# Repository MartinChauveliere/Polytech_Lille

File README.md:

# Projets Polytech Lille

Ce dépôt contient les projets réalisés dans le cadre de mes études à Polytech Lille, mon école d'ingénierie en France. 
Vous y trouverez différents projets liés à des domaines comme l'électronique, le code, et la conception de PCB.

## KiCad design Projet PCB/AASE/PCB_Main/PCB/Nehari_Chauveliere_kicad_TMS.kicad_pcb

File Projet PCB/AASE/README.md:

# AASE_Nehari_Chauveliere

## Objectif

L'obejctif initial de ce projet est de concevoir et réaliser la partie récepton d'une chaîne de réception en modulation numérique BPSK.

## Kicad schématique

Tout d'abord, nous avons dû créer notre carte électronique sur Kicad, pour cela nous sommes partis du précédent projet réalisé en TMS. De ce projet nous avons conservé le microcontrôleur (STM32) et le capteur de température (MCP9000) principalement.

Nous avons ensuite ajouté ce dont on avait besoin, c'est-à-dire :
- Quartz haute fréquence pour le STM32, MCSJK-7U-32.00-10-30-60-B-30;
- LDO positif pour convertir du +15V venant d'un générateur en +8V pour le démodulateur, AP7333-33SAG-7;
- LDO négatif pour convertir du -15V venant d'un générateur en -8V pour le démodulateur, MIC5271YM5-TR;
- Mosfet de puissance, XP161A1355PR-G;
- Convertisseur boost pour convertir du +1.8V venant d'une batterie vers du +3.3V, XC9103D095MR-G;
- Diode schottky pour le convertisseur boost, D0-214AC;
- Connecteurs divers.

## Kicad Rootage

Nous avons eu que très peu de soucis pour cette partie là.
Les tailles des pistes ont été choisies pour avoir une impédance adéquate.
Les plans de masse ont été placés de telle sorte à éviter la création d'antenne dans le PCB.
Nous avons aussi bien isolé les composants hautes fréquences du reste du circuit.

## Déphaseur

Plus tard, nous avons décidé de créer le circuit déphaseur du démodulateur BPSK.
Sur ce PCB, nous avons placé des connecteurs SMA car nous travaillons en haute fréquence.
La taille des pistes a été calculée pour avoir une impédance de 50 ohms

##Soudure et tests

Nous avons d'abord soudé les composants principaux afin de pouvoir tester simplement le clignotement d'une led.
Utilisation d'air chaud pour souder le quartz et de flux pour faciliter le travail.
Nous avons programmé le STM32 grâce à l'ide STM32CubeIDE.

Enfin, nous avons soudé le capteur de température, celui-ci nous donnant une valeur de 0.733V.
Selon la datasheet de ce capteur celaindique une température aux alentours des 20°c.
Nous pouvons donc en déduire qu'il fonctionne correctement.

## Consommation d'un STM32

Nous avons fait plusieurs tests sur la consommation d'une board Nucleo STM32 (résultats dans le dossier Vidéo consommation).
On peut noter que les résultats sur la consommation en fonction de la fréquence ne sont pas ceux espérés.
Nous aurions dû trouver une fonction en forme parabolique avec en sommet la fréquence idéale.

## Post-scriptum

A noter, que nous avons eu 4H de moins que les autres groupes car nous avons eu 3 séances de 4H avec Mr.Wichmann.

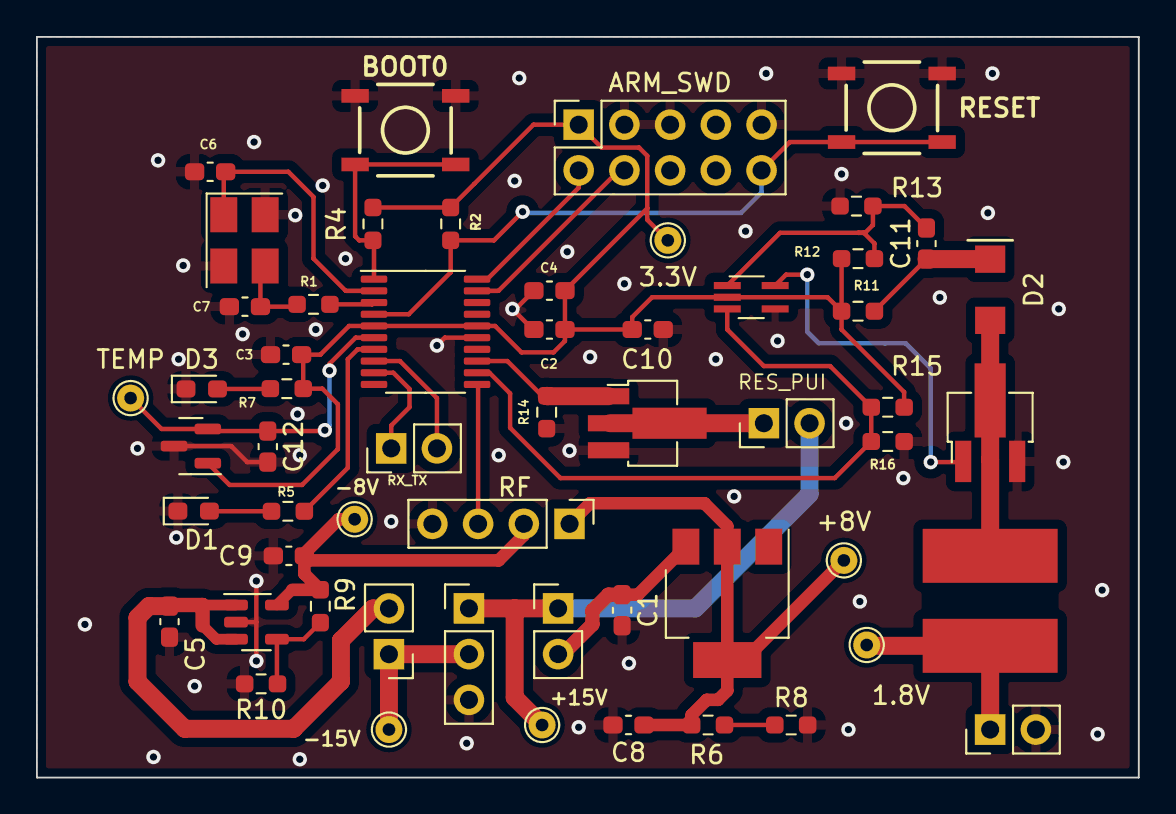
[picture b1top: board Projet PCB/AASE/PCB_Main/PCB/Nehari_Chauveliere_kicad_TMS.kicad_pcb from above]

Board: 2 copper layers, 61.2 x 41.1 mm, 56 parts (0 on the bottom side), 32 nets.

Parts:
1.8V, 3.3V: TestPoint; TestPoint_THTPad_D1.5mm_Drill0.7mm
+8V, +15V: TestPoint; TestPoint_THTPad_D1.5mm_Drill0.7mm
-8V, -15V: TestPoint; TestPoint_THTPad_D1.5mm_Drill0.7mm
ARM_SWD: Conn_ARM_JTAG_SWD_10; PinSocket_2x05_P2.54mm_Vertical
C1, C9: 10uF; C_0603_1608Metric_Pad1.08x0.95mm_HandSolder
C2, C5: 1uF; C_0603_1608Metric_Pad1.08x0.95mm_HandSolder
C3, C4: 100nF; C_0603_1608Metric_Pad1.08x0.95mm_HandSolder
C6, C7: 22pF; C_0603_1608Metric_Pad1.08x0.95mm_HandSolder
C8: 100uF; C_0603_1608Metric_Pad1.08x0.95mm_HandSolder
C10, C11, C12: C; C_0603_1608Metric_Pad1.08x0.95mm_HandSolder
D1, D3: LED; LED_0603_1608Metric_Pad1.05x0.95mm_HandSolder
D2: D_Schottky; Diode_schottky
J2: Conn_1.8V; PinHeader_1x02_P2.54mm_Vertical
J3: Conn_15V_-15V; PinHeader_1x03_P2.54mm_Vertical
J4: Conn2; PinHeader_1x02_P2.54mm_Vertical
J5: Conn1; PinHeader_1x02_P2.54mm_Vertical
L1: L; LD2-xxx-hv
Q1, Q2: Q_NMOS_GDS; SOT-89-3_Handsoldering
R1, R11, R12, R13, R14, R15, R16: R; R_0603_1608Metric_Pad0.98x0.95mm_HandSolder
R2, R4: 10k; R_0603_1608Metric_Pad0.98x0.95mm_HandSolder
R5, R7: 510; R_0603_1608Metric_Pad0.98x0.95mm_HandSolder
R6, R10: 100; R_0603_1608Metric_Pad0.98x0.95mm_HandSolder
R8, R9: 560; R_0603_1608Metric_Pad0.98x0.95mm_HandSolder
RES_PUI: Conn_01x02_Male; PinHeader_1x02_P2.54mm_Vertical
RF: Conn_RF; PinHeader_1x04_P2.54mm_Vertical
RX_TX: Conn_serial; PinHeader_1x02_P2.54mm_Vertical
S1, S2: MOMENTARY-SWITCH-SPST-2-SMD-5.2MM; TACTILE_SWITCH_SMD_5.2MM
TEMP: TestPoint; TestPoint_THTPad_D1.5mm_Drill0.7mm
U1: STM32F030F4Px; TSSOP-20_4.4x6.5mm_P0.65mm
U2: LM1117_SOT-223; SOT-223-3_TabPin2
U3: MCP9700T-ETT; SOT-23
U4: MIC5271YM5-TR; SOT-23-5
U5: XC9103D095MR-G; SOT-353_SC-70-5_Handsoldering
Y1: Crystal_GND24; Crystal_SMD_EuroQuartz_MT-4Pin_3.2x2.5mm_HandSoldering

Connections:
15_to_8: C1.1, J4.2, U2.3 (VI)
+3.3V: 3.3V.1, ARM_SWD.1 (VTref), C2.1, C3.1, C4.1, C10.1, R2.2, R4.2, R7.1, R11.1, R12.1, R15.1, U1.5 (VDDA), U1.16 (VDD), U3.1 (Vdd), U5.2 (VDD)
+8V: +8V.1, C8.1, R6.1, RF.1, U2.2 (VO)
+15V: +15V.1, J3.1, J4.1, RES_PUI.2
-8V: -8V.1, C9.1, R9.1, RF.2, U4.5 (OUT)
-15V: -15V.1, J3.2, J5.1
-15_to_-8: C5.1, J5.2, U4.1 (IN), U4.3 (EN)
BOOT: R4.1, S2.1, S2.2, U1.1 (BOOT0)
CE: R15.2, R16.1, U1.12 (PA6), U5.3 (CE)
GND: ARM_SWD.3 (GND), ARM_SWD.5 (GND), ARM_SWD.9 (GNDDetect), C1.2, C2.2, C3.2, C4.2, C5.2, C6.1, C7.1, C8.2, C9.2, C10.2, C12.2, D1.1 (K), D3.1 (K), J2.2, J3.3, Q1.3 (S), Q2.3 (S), R8.2, R10.2, R13.2, R14.2, R16.2, RF.4, S1.3, S1.4, S2.3, S2.4, U1.15 (VSS), U3.3 (GND), U4.2 (GND), U5.4 (GND), Y1.2, Y1.4
LED_TEST1: R5.1, U1.7 (PA1)
MOS: Q2.1 (G), R14.1, U1.13 (PA7)
unnamed: C7.2, R1.2, Y1.3
unnamed: C11.1, D2.1 (K), R11.2
unnamed: C11.2, R12.2, R13.1, U5.1 (FB)
unnamed: D1.2 (A), R5.2
unnamed: D2.2 (A), L1.1, Q1.2 (D)
unnamed: D3.2 (A), R7.2
unnamed: Q2.2 (D), RES_PUI.1
unnamed: Q1.1 (G), U5.5 (EXT)
unnamed: R6.2, R8.1
unnamed: R9.2, R10.1, U4.4 (BP)
OSC_IN: C6.2, U1.2 (PF0), Y1.1
OSC_OUT: R1.1, U1.3 (PF1)
RF_comm: RF.3, U1.11 (PA5)
RST: ARM_SWD.10 (~RESET), R2.1, S1.1, S1.2, U1.4 (NRST)
RX: RX_TX.1, U1.9 (PA3)
SWCLK: ARM_SWD.2 (SWDIO/TMS), U1.20 (PA14)
SWDAT: ARM_SWD.4 (SWDCLK/TCK), U1.19 (PA13)
TEMP_OUT: C12.1, TEMP.1, U1.6 (PA0), U3.2 (Vout)
TX: RX_TX.2, U1.8 (PA2)
V_1.8V: 1.8V.1, J2.1, L1.2

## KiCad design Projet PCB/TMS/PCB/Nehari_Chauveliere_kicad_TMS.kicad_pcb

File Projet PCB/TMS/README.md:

# Projet PCB - STM32F030F4Px

**Conception d'un circuit imprimé (PCB) avec KiCad**  
**Durée totale estimée : 4 heures**

---

## Composants principaux

- **Microcontrôleur** : STM32F030F4Px  
- **Capteur de température** : MCP9700T-ETT (boîtier SOT-23-3)  
- **Mémoire** : M24C01-RDW  
- **LEDs de test**  
- **Condensateurs de découplage** : valeur à définir (F)

---

## Chronologie du projet

### 1ère heure - Choix des composants & Schéma électrique

- Sélection et ajout des composants dans KiCad.
- Lecture des datasheets pour configurer correctement les connexions.
- **Notes importantes** :
  - **M24C01-RDW** : Les bits **E0**, **E1**, **E2** (Chip Enable) doivent être fixés à **0** pour permettre la communication (valable pour le package **DFN5**).
- Début de la création du schéma électrique (`Schematic`) à partir des spécifications des datasheets.

---

### 2ème heure - Outils supplémentaires et finalisation du schéma

- **Installation de la librairie SparkFun** pour ajouter un bouton Reset au microcontrôleur.
- Utilisation de l'**ASN4325** pour la configuration précise du schéma du contrôleur.
- Finalisation du schéma (reportée en partie à la 3ème heure).

---

### 3ème heure - Interface de programmation et préparation PCB

- Passage de la programmation via **SWD** (Serial Wire Debug) au lieu de l'**AVR ISP** (suppression du connecteur ISP).
- Ajout du **footprint pour le quartz** : **HC49**.
- Conception du schéma du connecteur SWD.
- Finalisation du schéma électrique complet.
- Attribution des **footprints** aux composants.
- Début du **routage PCB**.

---

### 4ème heure - Finalisation

- Fin du **routage du PCB**.
- Génération des fichiers de fabrication (`Gerber files`).
- Envoi du projet en fabrication.

---

## Programmation

En suivant les étapes données par le sujet et le site :  
[https://linuxembedded.fr/2021/02/bare-metal-from-zero-to-blink](https://linuxembedded.fr/2021/02/bare-metal-from-zero-to-blink)

Nous sommes parvenus à :

- Écrire la configuration de la carte (`stm32_startup.c`, `main.c` et `final.map`)
- Créer la librairie `stm32_ls.ld`

Dans cette configuration, nous avons :

- Défini la table de vecteurs
- Initialisé la pile
- Initialisé le segment BSS

**Remarques** :

- Le tutoriel comprenait quelques erreurs à repérer (au niveau des caractères) et quelques adaptations étaient nécessaires (par exemple la fréquence).
- Nous avons finalement réussi à flasher notre code dans la carte (à l'aide de `gdb`).
- Cependant, nous suspectons une maladresse au niveau de la soudure qui nous a empêchés de voir la LED clignoter.

Ce qui reste certain est que le code a bien été flashé dans la carte !

---

## Infos supplémentaires

- Outils utilisés : **KiCad** (v6 ou v7 recommandé)
- Technologies de communication : **SWD** pour la programmation et le debug du STM32.
- Important : vérifier les tensions de fonctionnement compatibles entre tous les composants.

---

## À faire (améliorations possibles)

- Définir précisément la valeur des condensateurs de découplage.
- Ajouter des protections ESD si nécessaire.
- Vérifier les largeurs de pistes selon l'intensité prévue (règles IPC-2221).

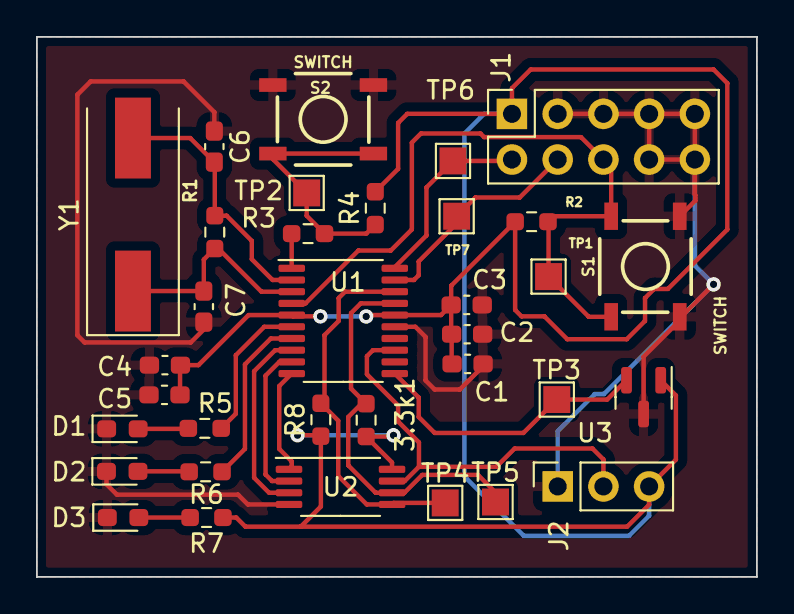
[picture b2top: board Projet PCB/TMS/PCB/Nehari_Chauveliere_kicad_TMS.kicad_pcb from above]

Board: 2 copper layers, 40.0 x 30.0 mm, 34 parts (0 on the bottom side), 21 nets.

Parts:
3.3k1: R; R_0603_1608Metric_Pad0.98x0.95mm_HandSolder
C1, C5: 10nF; C_0603_1608Metric_Pad1.08x0.95mm_HandSolder
C2: 4.7uF; C_0603_1608Metric_Pad1.08x0.95mm_HandSolder
C3: 100nF; C_0603_1608Metric_Pad1.08x0.95mm_HandSolder
C4: 1uF; C_0603_1608Metric_Pad1.08x0.95mm_HandSolder
C6, C7: 22pF; C_0603_1608Metric_Pad1.08x0.95mm_HandSolder
D1, D2, D3: LED; LED_0603_1608Metric_Pad1.05x0.95mm_HandSolder
J1: Conn_ARM_JTAG_SWD_10; PinSocket_2x05_P2.54mm_Vertical
J2: Conn_01x03_Male; PinSocket_1x03_P2.54mm_Vertical
R1: R; R_0603_1608Metric_Pad0.98x0.95mm_HandSolder
R2, R3, R4: 10k; R_0603_1608Metric_Pad0.98x0.95mm_HandSolder
R5, R6, R7: 510; R_0603_1608Metric_Pad0.98x0.95mm_HandSolder
R8: 3.3k; R_0603_1608Metric_Pad0.98x0.95mm_HandSolder
S1, S2: SWITCH; TACTILE_SWITCH_SMD_5.2MM
TP1, TP2, TP3, TP4, TP5, TP6, TP7: TestPoint; TestPoint_Pad_1.5x1.5mm
U1: STM32F030F4Px; TSSOP-20_4.4x6.5mm_P0.65mm
U2: M24C01-RDW; TSSOP-8_4.4x3mm_P0.65mm
U3: MCP9700T-ETT; SOT-23
Y1: Crystal; Crystal_SMD_HC49-SD

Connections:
BOOT: R3.1, U1.1 (BOOT0)
Bit1: U1.10 (PA4), U2.1 (E0)
Bit2: U1.9 (PA3), U2.2 (E1)
Bit3: U1.8 (PA2), U2.3 (E2)
GND: C1.2, C2.2, C3.2, C4.2, C5.2, C6.1, C7.1, D1.1 (K), D2.1 (K), D3.1 (K), J1.3 (GND), J1.5 (GND), J1.7 (KEY), J1.8 (NC/TDI), J1.9 (GNDDetect), J1.10 (~RESET), J2.1, S1.3, S1.4, S2.3, S2.4, U1.15 (VSS), U2.4 (VSS), U3.3 (GND)
LED_TEST1: R5.1, U1.6 (PA0)
LED_TEST2: R6.1, U1.7 (PA1)
unnamed: D1.2 (A), R5.2
unnamed: D2.2 (A), R6.2
unnamed: D3.2 (A), R7.2
unnamed: R3.2, R4.1, S2.1, S2.2, TP2.1
OSC_IN: C6.2, R1.1, U1.2 (PF0), Y1.2
OSC_OUT: C7.2, R1.2, U1.3 (PF1), Y1.1
RST: J1.6 (SWO/TDO), R2.1, S1.1, S1.2, TP1.1, U1.4 (NRST)
SWCLK: J1.2 (SWDIO/TMS), TP6.1, U1.20 (PA14)
SWDAT: J1.4 (SWDCLK/TCK), TP7.1, U1.19 (PA13)
Serial_clock: 3.3k1.2, TP5.1, U1.17 (PA9), U2.6 (SCL)
Serial_data: R8.2, TP4.1, U1.18 (PA10), U2.5 (SDA)
VCC: 3.3k1.1, C1.1, C2.1, C3.1, C4.1, C5.1, J1.1 (VTref), J2.3, R2.2, R4.2, R7.1, R8.1, U1.5 (VDDA), U1.16 (VDD), U2.8 (VCC), U3.1 (Vdd)
V_OUT: TP3.1, U1.11 (PA5), U3.2 (Vout)
Write_enable: J2.2, U1.13 (PA7), U2.7 (~WC)

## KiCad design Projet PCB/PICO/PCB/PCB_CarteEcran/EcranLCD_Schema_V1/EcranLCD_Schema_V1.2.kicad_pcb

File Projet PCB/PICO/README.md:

# Projet Pico-ordinateur

## Contexte du projet

Le projet s'inscrit dans le cadre du développement d'un **Pico-ordinateur**, suivant les consignes et objectifs détaillés sur le site :  
[https://projets-se.plil.fr/mediawiki/index.php/Pico-ordinateur](https://projets-se.plil.fr/mediawiki/index.php/Pico-ordinateur)

L'objectif est de concevoir un système informatique embarqué minimaliste capable de remplir des fonctions basiques tout en respectant de fortes contraintes matérielles et logicielles.

## Wiki de notre projet

Le développement de notre binôme, les choix techniques, l'avancement du projet ainsi que les ressources associées sont documentés dans notre espace Wiki :  
[https://projets-se.plil.fr/mediawiki/index.php/SE4Binome2023-1](https://projets-se.plil.fr/mediawiki/index.php/SE4Binome2023-1)

Vous y trouverez toutes les informations nécessaires pour comprendre notre démarche et reproduire notre travail.

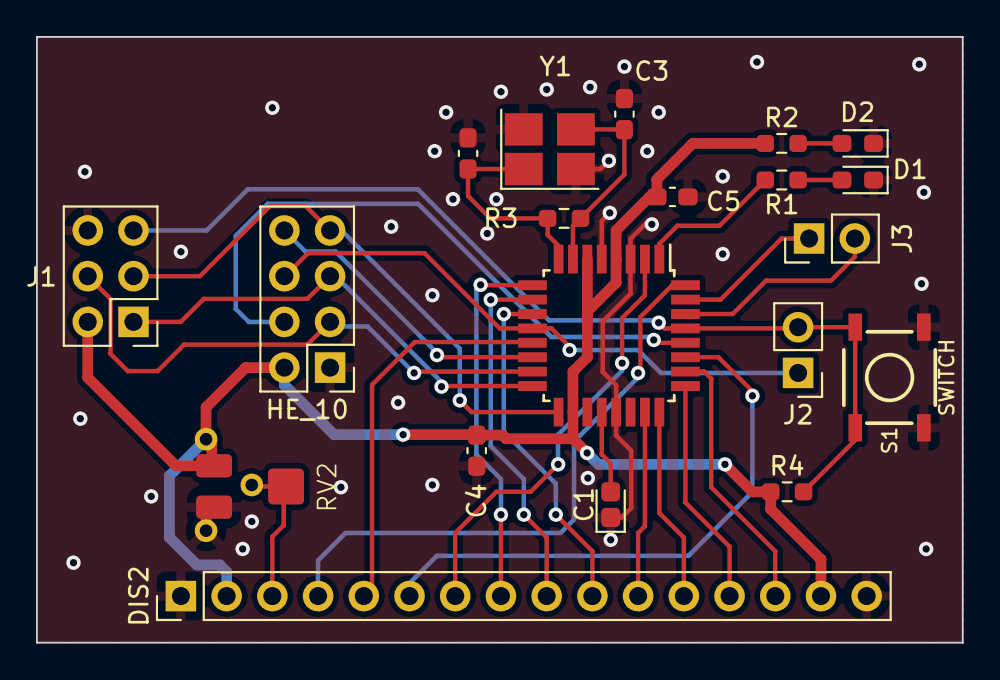
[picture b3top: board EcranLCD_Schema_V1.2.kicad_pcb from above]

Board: 2 copper layers, 51.4 x 33.7 mm, 21 parts (1 on the bottom side), 29 nets.

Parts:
C1: 100nF; CP_EIA-1608-08_AVX-J
C2, C3: 22pF; C_0603_1608Metric_Pad1.08x0.95mm_HandSolder
C4, C5: 100nF; C_0603_1608Metric_Pad1.08x0.95mm_HandSolder
D1, D2: LED; LED_0603_1608Metric_Pad1.05x0.95mm_HandSolder
DIS2: HD44780; PinHeader_1x16_P2.54mm_Vertical
HE_10: Conn_02x04_Counter_Clockwise; PinHeader_2x04_P2.54mm_Vertical
J1: AVR-ISP-6; PinHeader_2x03_P2.54mm_Vertical
J2: Conn_01x02_Pin_RST; PinHeader_1x02_P2.54mm_Vertical
J3: Conn_01x02_Pin_RxTx; PinHeader_1x02_P2.54mm_Vertical
R1, R2: 510; R_0603_1608Metric_Pad0.98x0.95mm_HandSolder
R3: R; R_0603_1608Metric_Pad0.98x0.95mm_HandSolder
R4: 10k; R_0603_1608Metric_Pad0.98x0.95mm_HandSolder
RV1: R_Potentiometer; Potentiometer_Bourns_3339P_Vertical
RV2: R_Potentiometer; Potentiometre
S1: SWITCH; TACTILE_SWITCH_SMD_5.2MM
U2: ATmega328P-A; TQFP-32_7x7mm_P0.8mm
Y1: 8Mhz; Crystal_SMD_SeikoEpson_FA238-4Pin_3.2x2.5mm_HandSoldering

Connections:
+5V: C4.1, C5.2, DIS2.2, DIS2.15, HE_10.2, J1.2 (VCC), R2.1, R4.1, RV1.3, RV2.3, U2.4 (VCC), U2.6 (VCC), U2.18 (AVCC)
BIT0: DIS2.7, U2.2 (PD4)
BIT1: DIS2.8, U2.9 (PD5)
BIT2: DIS2.9, U2.10 (PD6)
BIT3: DIS2.10, U2.11 (PD7)
BIT4: DIS2.11, U2.23 (PC0)
BIT5: DIS2.12, U2.24 (PC1)
BIT6: DIS2.13, U2.25 (PC2)
BIT7: DIS2.14, U2.26 (PC3)
CS: HE_10.8, U2.14 (PB2)
ENABLE: DIS2.6, U2.27 (PC4)
GND: C1.1, C2.2, C3.2, C4.2, C5.1, D1.1 (K), D2.1 (K), DIS2.1, DIS2.16, HE_10.1, J1.6 (GND), RV1.1, RV2.1, S1.3, S1.4, U2.3 (GND), U2.5 (GND), U2.21 (GND), Y1.2, Y1.4
Interruption: HE_10.4, U2.28 (PC5)
Led_Test: R1.1, U2.1 (PD3)
MISO: HE_10.5, J1.1 (MISO), U2.16 (PB4)
MOSI: HE_10.3, J1.4 (MOSI), U2.15 (PB3)
unnamed: D1.2 (A), R1.2
unnamed: D2.2 (A), R2.2
unnamed: DIS2.3, RV1.2, RV2.2
unnamed: C1.2, U2.20 (AREF)
RS: DIS2.4, U2.32 (PD2)
RST: HE_10.6, J2.1, U2.12 (PB0)
RSTISP: J1.5 (~RST), J2.2, R4.2, S1.1, S1.2, U2.29 (~RESET/PC6)
RX: J3.2, U2.30 (PD0)
R/W: DIS2.5, U2.13 (PB1)
SCK: HE_10.7, J1.3 (SCK), U2.17 (PB5)
TX: J3.1, U2.31 (PD1)
XTAL1: C3.1, R3.1, U2.7 (XTAL1/PB6), Y1.3
XTAL2: C2.1, R3.2, U2.8 (XTAL2/PB7), Y1.1

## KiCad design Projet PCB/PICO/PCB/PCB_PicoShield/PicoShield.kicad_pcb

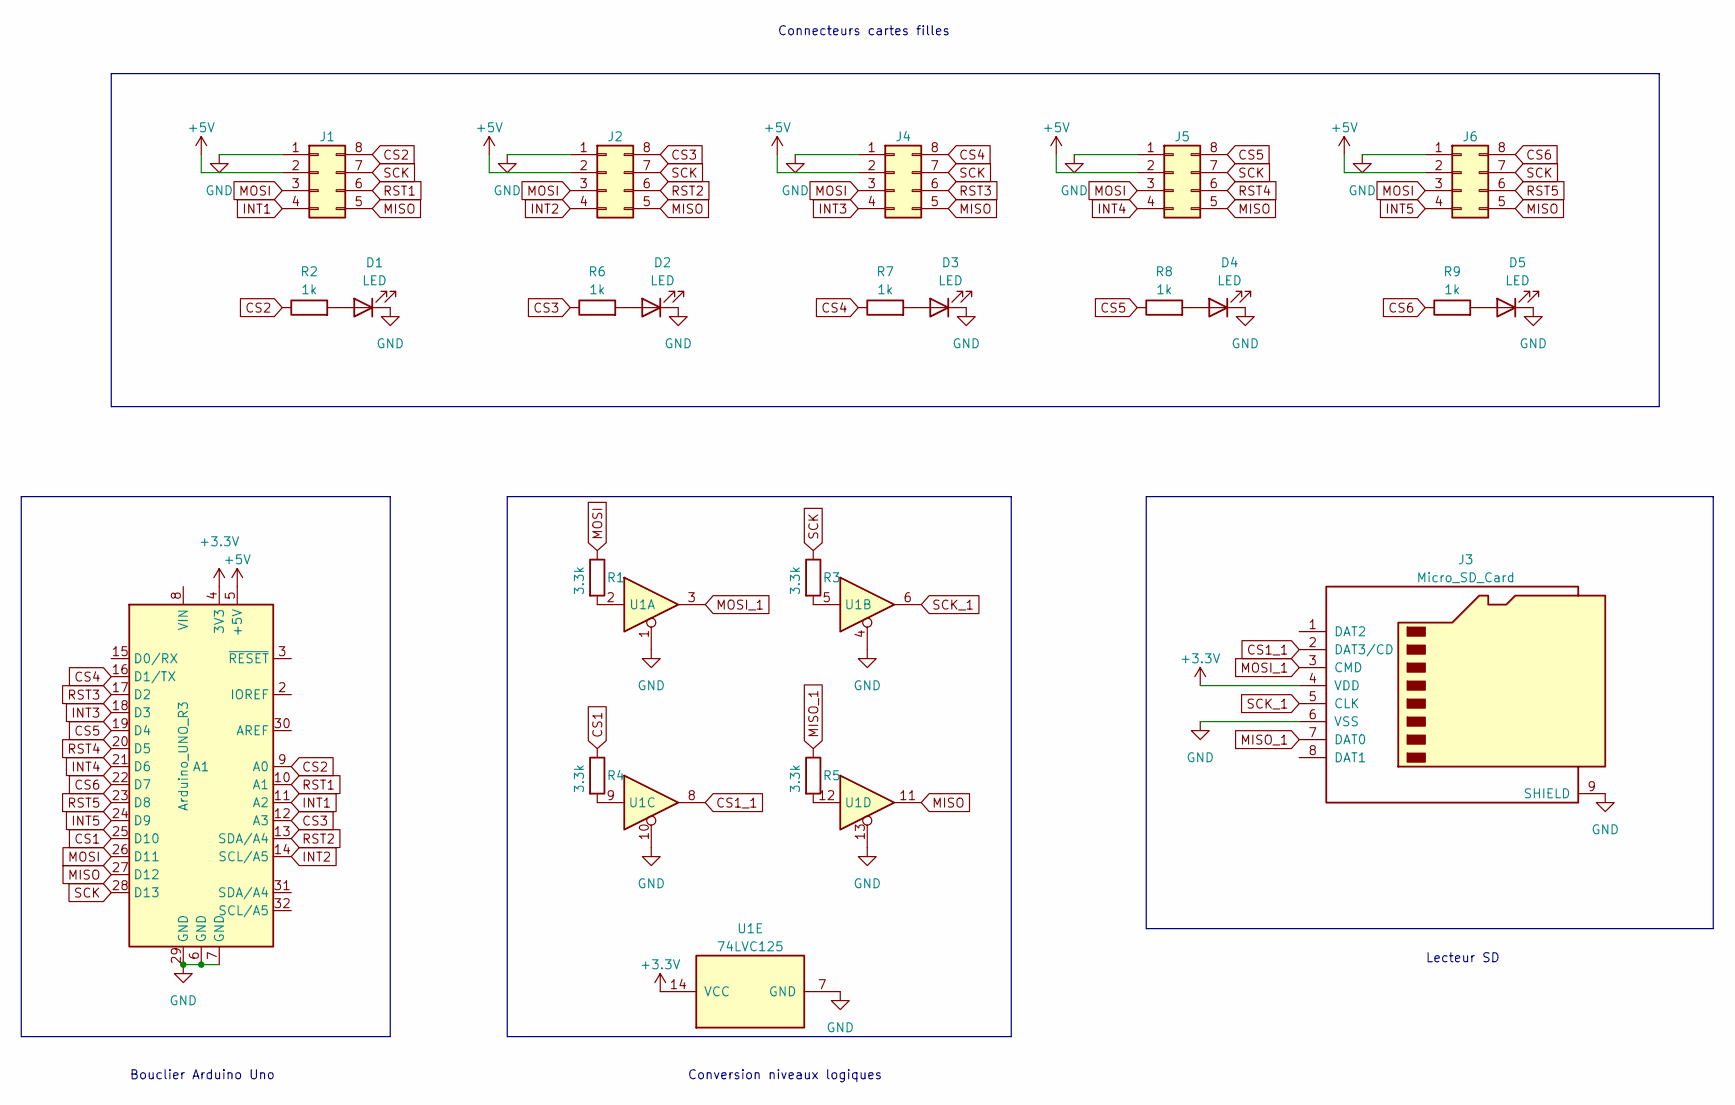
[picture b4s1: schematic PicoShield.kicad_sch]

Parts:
A1: Arduino_UNO_R3
D1, D2, D3, D4, D5: LED; LED_0603_1608Metric_Pad1.05x0.95mm_HandSolder
J1, J2, J4, J5, J6: Conn_02x04_Counter_Clockwise; PinHeader_2x04_P2.54mm_Vertical
J3: Micro_SD_Card; microSD_HC_Hirose_DM3D-SF
R1, R3, R4, R5: 3.3k; R_0603_1608Metric_Pad0.98x0.95mm_HandSolder
R2, R6, R7, R8, R9: 1k; R_0603_1608Metric_Pad0.98x0.95mm_HandSolder
U1: 74LVC125; SOIC-14_3.9x8.7mm_P1.27mm

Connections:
+3V3: A1.4 (3V3), J3.4 (VDD), U1.14 (VCC)
+5V: A1.5 (+5V), J1.2, J2.2, J4.2, J5.2, J6.2
CS1: A1.25 (D10), R4.1
CS1_1: J3.2 (DAT3/CD), U1.8
CS2: A1.9 (A0), J1.8, R2.1
CS3: A1.12 (A3), J2.8, R6.1
CS4: A1.16 (D1/TX), J4.8, R7.1
CS5: A1.19 (D4), J5.8, R8.1
CS6: A1.22 (D7), J6.8, R9.1
GND: A1.6 (GND), A1.7 (GND), A1.29 (GND), D1.1 (K), D2.1 (K), D3.1 (K), D4.1 (K), D5.1 (K), J1.1, J2.1, J3.6 (VSS), J3.9 (SHIELD), J4.1, J5.1, J6.1, U1.1, U1.4, U1.7 (GND), U1.10, U1.13
INT1: A1.11 (A2), J1.4
INT2: A1.14 (SCL/A5), J2.4
INT3: A1.18 (D3), J4.4
INT4: A1.21 (D6), J5.4
INT5: A1.24 (D9), J6.4
MISO: A1.27 (D12), J1.5, J2.5, J4.5, J5.5, J6.5, U1.11
MISO_1: J3.7 (DAT0), R5.1
MOSI: A1.26 (D11), J1.3, J2.3, J4.3, J5.3, J6.3, R1.1
MOSI_1: J3.3 (CMD), U1.3
unnamed: D1.2 (A), R2.2
unnamed: D2.2 (A), R6.2
unnamed: D3.2 (A), R7.2
unnamed: D4.2 (A), R8.2
unnamed: D5.2 (A), R9.2
unnamed: R1.2, U1.2
unnamed: R3.2, U1.5
unnamed: R4.2, U1.9
unnamed: R5.2, U1.12
RST1: A1.10 (A1), J1.6
RST2: A1.13 (SDA/A4), J2.6
RST3: A1.17 (D2), J4.6
RST4: A1.20 (D5), J5.6
RST5: A1.23 (D8), J6.6
SCK: A1.28 (D13), J1.7, J2.7, J4.7, J5.7, J6.7, R3.1
SCK_1: J3.5 (CLK), U1.6

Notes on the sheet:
Lecteur SD
Connecteurs cartes filles
Conversion niveaux logiques
Bouclier Arduino Uno

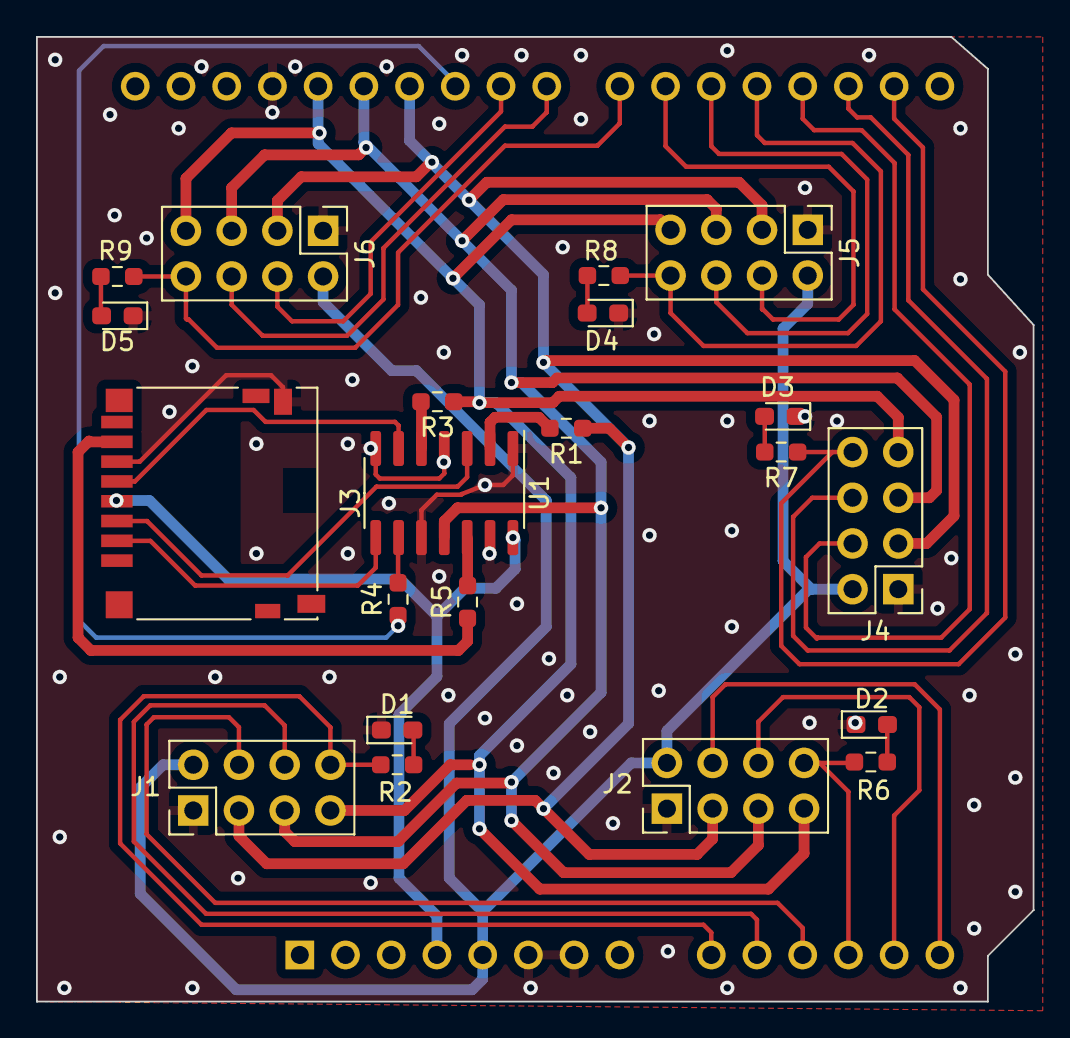
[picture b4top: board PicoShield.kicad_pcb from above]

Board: 2 copper layers, 55.4 x 53.6 mm, 22 parts (1 on the bottom side), 35 nets.

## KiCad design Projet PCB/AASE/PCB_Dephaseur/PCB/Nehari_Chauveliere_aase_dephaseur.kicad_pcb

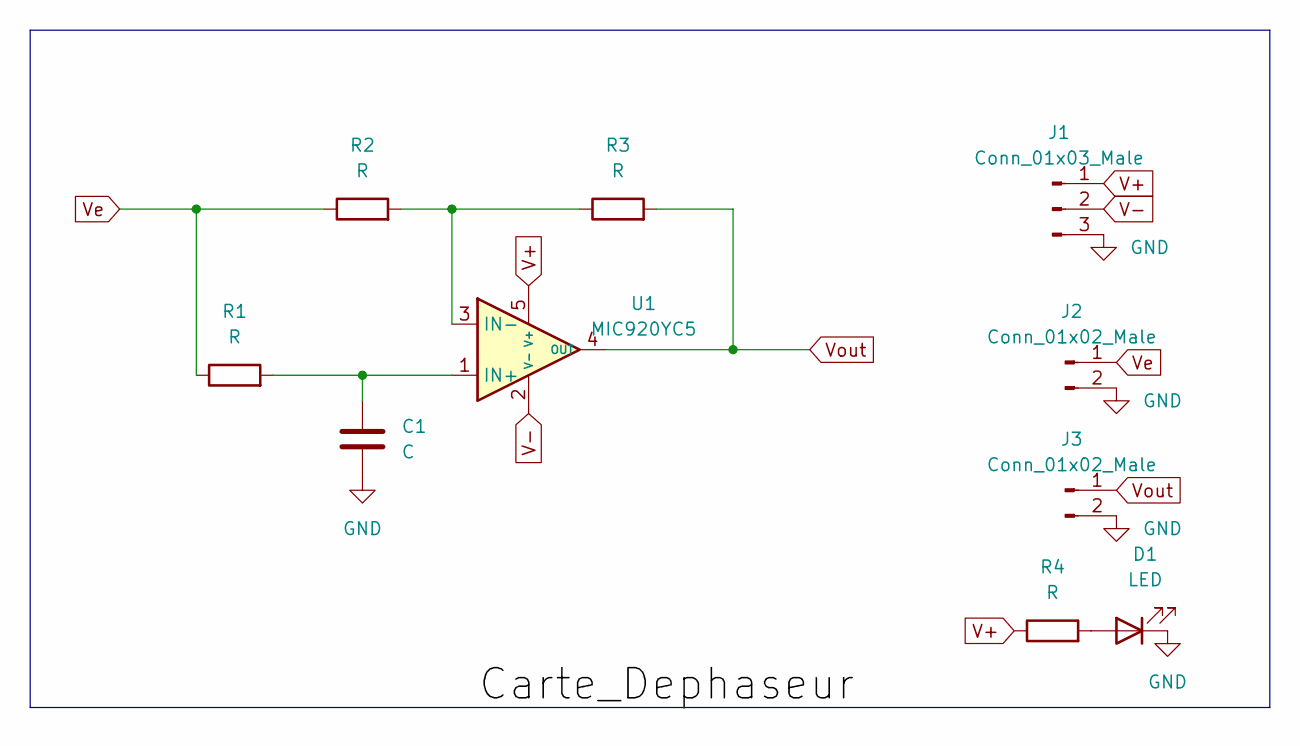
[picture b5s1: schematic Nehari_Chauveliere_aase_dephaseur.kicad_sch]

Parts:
C1: C; C_0603_1608Metric_Pad1.08x0.95mm_HandSolder
D1: LED; LED_0603_1608Metric_Pad1.05x0.95mm_HandSolder
J1: Conn_01x03_Male; PinHeader_1x03_P2.54mm_Vertical
J2, J3: Conn_01x02_Male; SMA_Molex_73251-2200_Horizontal
R1, R2, R3, R4: R; R_0603_1608Metric_Pad0.98x0.95mm_HandSolder
U1: MIC920YC5; SOT-353_SC-70-5_Handsoldering

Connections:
GND: C1.2, D1.1 (K), J1.3, J2.2, J3.2
unnamed: C1.1, R1.2, U1.1 (IN+)
unnamed: D1.2 (A), R4.2
unnamed: R2.2, R3.1, U1.3 (IN-)
V+: J1.1, R4.1, U1.5 (V+)
V-: J1.2, U1.2 (V-)
Ve: J2.1, R1.1, R2.1
Vout: J3.1, R3.2, U1.4 (OUT)

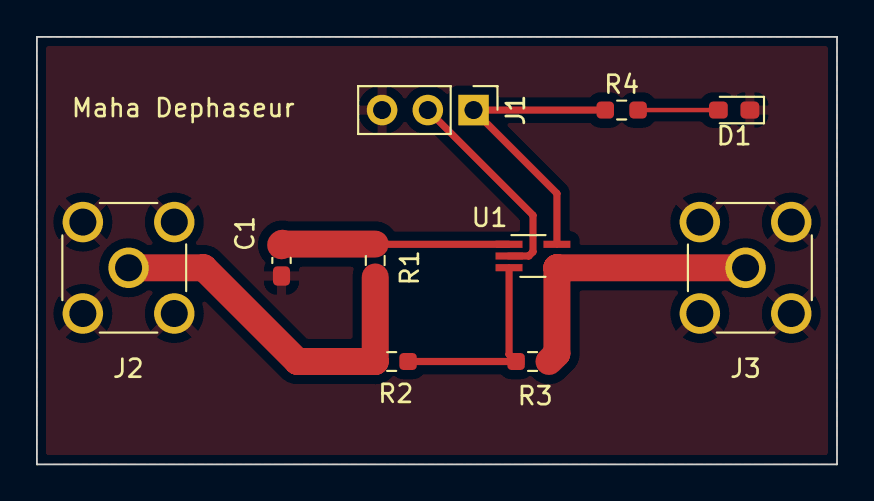
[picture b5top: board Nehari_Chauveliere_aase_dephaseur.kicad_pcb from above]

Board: 2 copper layers, 44.4 x 23.7 mm, 10 parts (0 on the bottom side), 8 nets.

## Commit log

2025-04-28 Push Projects
